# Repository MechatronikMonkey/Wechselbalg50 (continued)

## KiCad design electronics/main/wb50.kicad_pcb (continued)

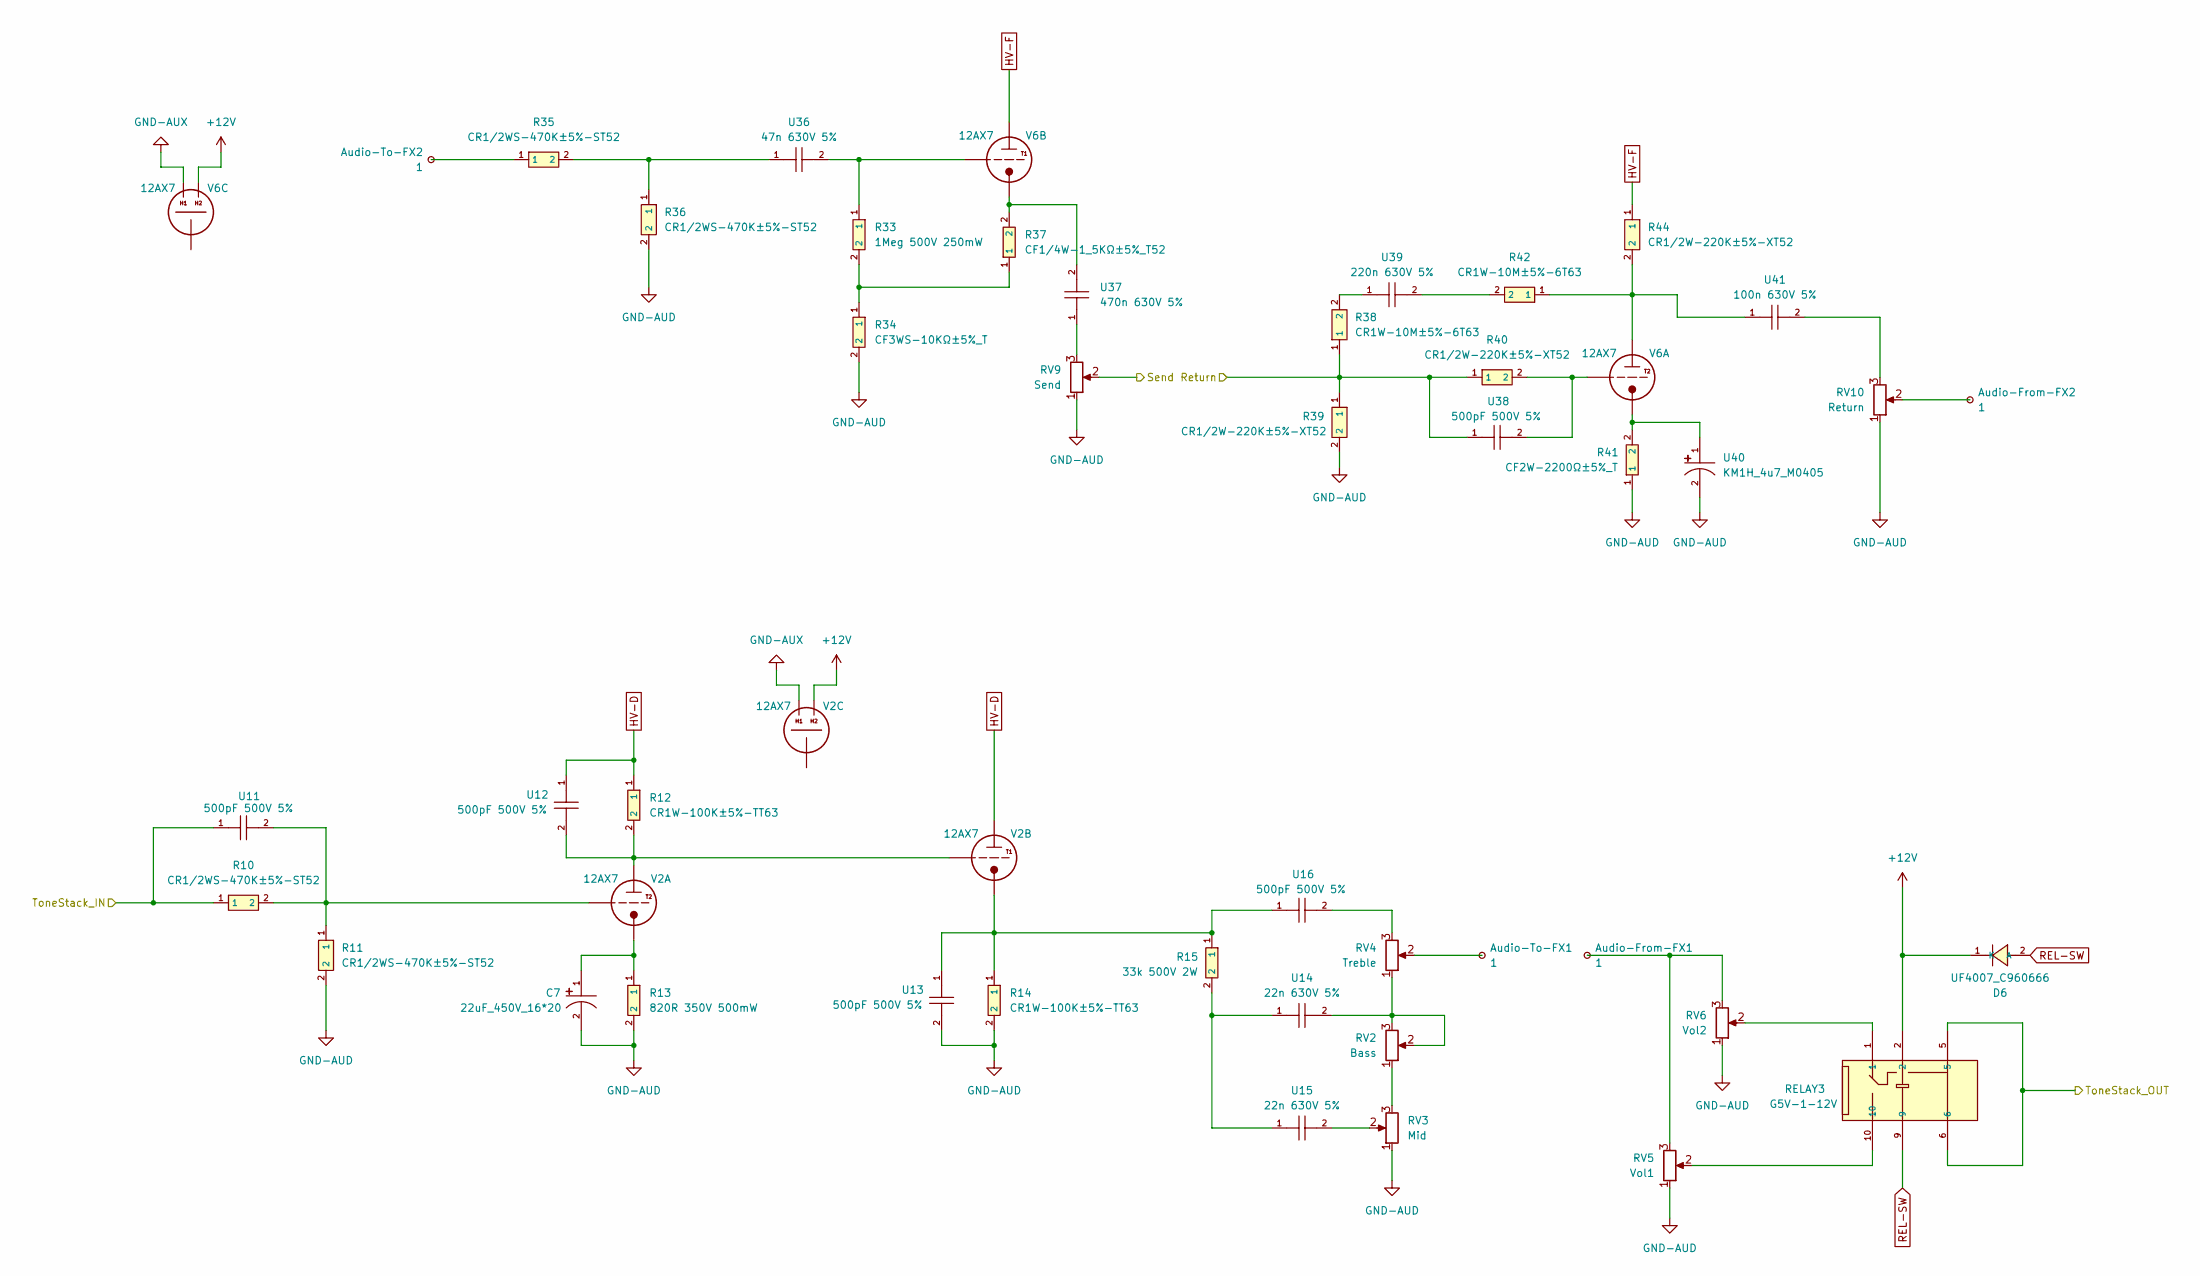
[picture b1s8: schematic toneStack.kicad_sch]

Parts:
Audio-From-FX1, Audio-From-FX2: 1; TestPoint_THTPad_D3.0mm_Drill1.5mm
Audio-To-FX1, Audio-To-FX2: 1; TestPoint_THTPad_D3.0mm_Drill1.5mm
C7: 22uF_450V_16*20; CAP-TH_BD16.0-P7.50-D1.2-FD; LCSC C10737
D6: UF4007_C960666; DO-41_BD2.4-L4.7-P8.70-D0.9-RD; LCSC C960666
R10, R11, R35, R36: CR1/2WS-470K±5%-ST52; RES-TH_BD2.7-L6.2-P10.20-D0.4; LCSC C2857409
R12, R14: CR1W-100K±5%-TT63; RES-TH_BD4.5-L11.0-P15.00-D0.7; LCSC C601829
R13: 820R 350V 500mW; RES-TH_BD4.0-L10.5-P14.50-D0.6; LCSC C167619
R15: 33k 500V 2W; RES-TH_BD3.0-L9.5-P13.50-D0.6; LCSC C70845
R33: 1Meg 500V 250mW; RES-TH_BD2.4-L6.3-P10.30-D0.6; LCSC C1370556
R34: CF3WS-10KΩ±5%_T; RES-TH_BD5.5-L15.0-P19.00-D0.8; LCSC C120810
R37: CF1/4W-1_5KΩ±5%_T52; RES-TH_BD2.3-L6.5-P10.50-D0.5; LCSC C120059
R38, R42: CR1W-10M±5%-6T63; RES-TH_BD4.5-L11.0-P15.00-D0.7; LCSC C2897121
R39, R40, R44: CR1/2W-220K±5%-XT52; RES-TH_BD3.5-L9.0-P13.00-D0.5; LCSC C2894491
R41: CF2W-2200Ω±5%_T; RES-TH_BD5.5-L15.0-P19.00-D0.8; LCSC C187501
RELAY3: G5V-1-12V; RELAY-TH_G5V-1; LCSC C31113
RV2: Bass; WB50_Pot_Omeg_PC20BU_P5.00mm
RV3: Mid; WB50_Pot_Omeg_PC20BU_P5.00mm
RV4: Treble; WB50_Pot_Omeg_PC20BU_P5.00mm
RV5: Vol1; WB50_Pot_Omeg_PC20BU_P5.00mm
RV6: Vol2; WB50_Pot_Omeg_PC20BU_P5.00mm
RV9: Send; WB50_Pot_Omeg_PC20BU_P5.00mm
RV10: Return; WB50_Pot_Omeg_PC20BU_P5.00mm
U11, U12, U13, U16, U38: 500pF 500V 5%; MICA_CAP_L15.5_W3.6_P8.7
U14, U15: 22n 630V 5%; MUSTARD_CAP_D8.5_L20.5_P25.5
U36: 47n 630V 5%; MUSTARD_CAP_D8.5_L20.5_P25.5
U37: 470n 630V 5%; MUSTARD_CAP_D10_L32_P40.4
U39: 220n 630V 5%; MUSTARD_CAP_D10_L32_P40.4
U40: KM1H_4u7_M0405; CAP-TH_BD4.0-P1.50-D0.5-FD; LCSC C2873979
U41: 100n 630V 5%; MUSTARD_CAP_D10_L32_P40.4
V2, V6: 12AX7; WB50_Socket_Noval_9Pin_D21.0mm_Hole1.8mm

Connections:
+12V: D6.1 (K), RELAY3.2, V2.4 (H1), V6.4 (H1); also elsewhere on the board
/Connectors/Return: R38.1, R39.1, R40.1, U38.1; also elsewhere on the board
/Connectors/Send: RV9.2; also elsewhere on the board
/Phase Inverter/PI_IN: RELAY3.5, RELAY3.6; also elsewhere on the board
/Pre Amp/PreAmp_OUT: R10.1, U11.1; also elsewhere on the board
GND-AUD: C7.2, R11.2, R13.2, R14.2, R34.2, R36.2, R39.2, R41.1, RV3.1, RV5.1, RV6.1, RV9.1, RV10.1, U13.2, U40.2; also elsewhere on the board
GND-AUX: V2.5 (H2), V6.5 (H2); also elsewhere on the board
HV-D: R12.1, U12.1, V2.6 (A/P); also elsewhere on the board
HV-F: R44.1, V6.6 (A/P); also elsewhere on the board
unnamed: Audio-From-FX1.1, RV5.3, RV6.3
unnamed: Audio-From-FX2.1, RV10.2
unnamed: Audio-To-FX1.1, RV4.2
unnamed: Audio-To-FX2.1, R35.1
unnamed: R15.2, U14.1, U15.1
unnamed: R33.2, R34.1, R37.1
unnamed: R35.2, R36.1, U36.1
unnamed: R38.2, U39.1
unnamed: R42.2, U39.2
unnamed: RELAY3.1, RV6.2
unnamed: RELAY3.10, RV5.2
unnamed: RV2.1, RV3.3
unnamed: RV2.2, RV2.3, RV4.1, U14.2
unnamed: RV3.2, U15.2
unnamed: RV4.3, U16.2
unnamed: RV9.3, U37.1
unnamed: RV10.3, U41.2
unnamed: R12.2, U12.2, V2.1 (A/P), V2.7 (G)
unnamed: C7.1, R13.1, V2.3 (C/K)
unnamed: R10.2, R11.1, U11.2, V2.2 (G)
unnamed: R14.1, R15.1, U13.1, U16.1, V2.8 (C/K)
unnamed: R42.1, R44.2, U41.1, V6.1 (A/P)
unnamed: R41.2, U40.1, V6.3 (C/K)
unnamed: R40.2, U38.2, V6.2 (G)
unnamed: R37.2, U37.2, V6.8 (C/K)
unnamed: R33.1, U36.2, V6.7 (G)
REL-SW: D6.2 (A), RELAY3.9; also elsewhere on the board

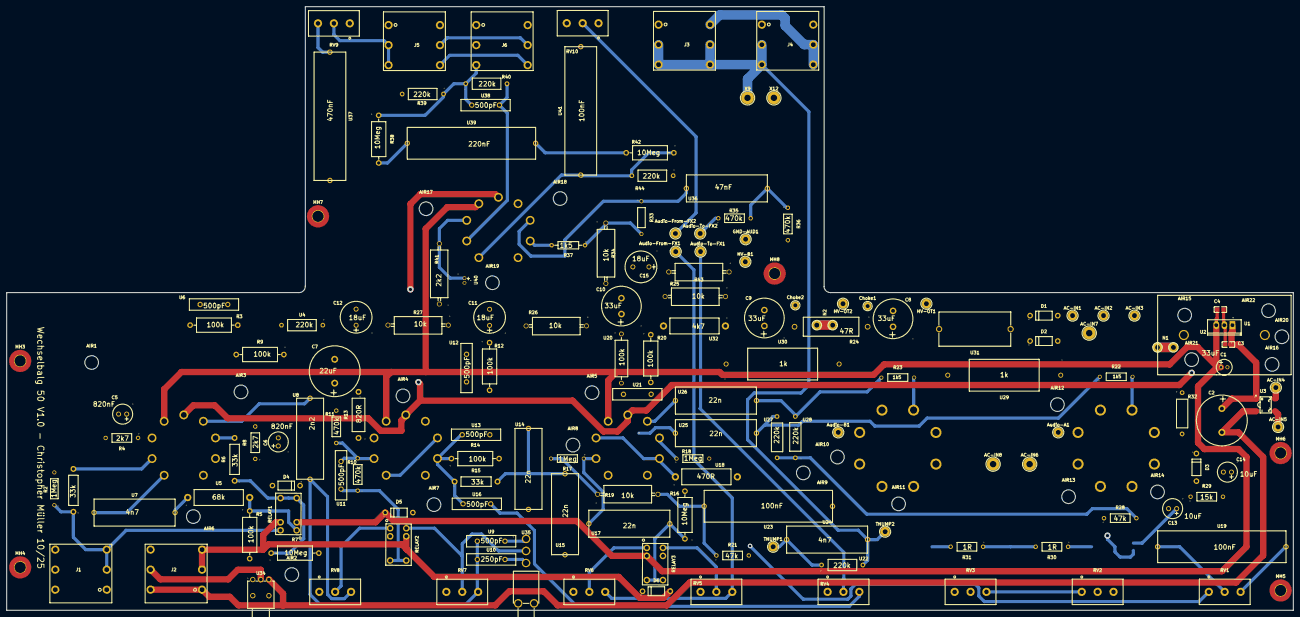
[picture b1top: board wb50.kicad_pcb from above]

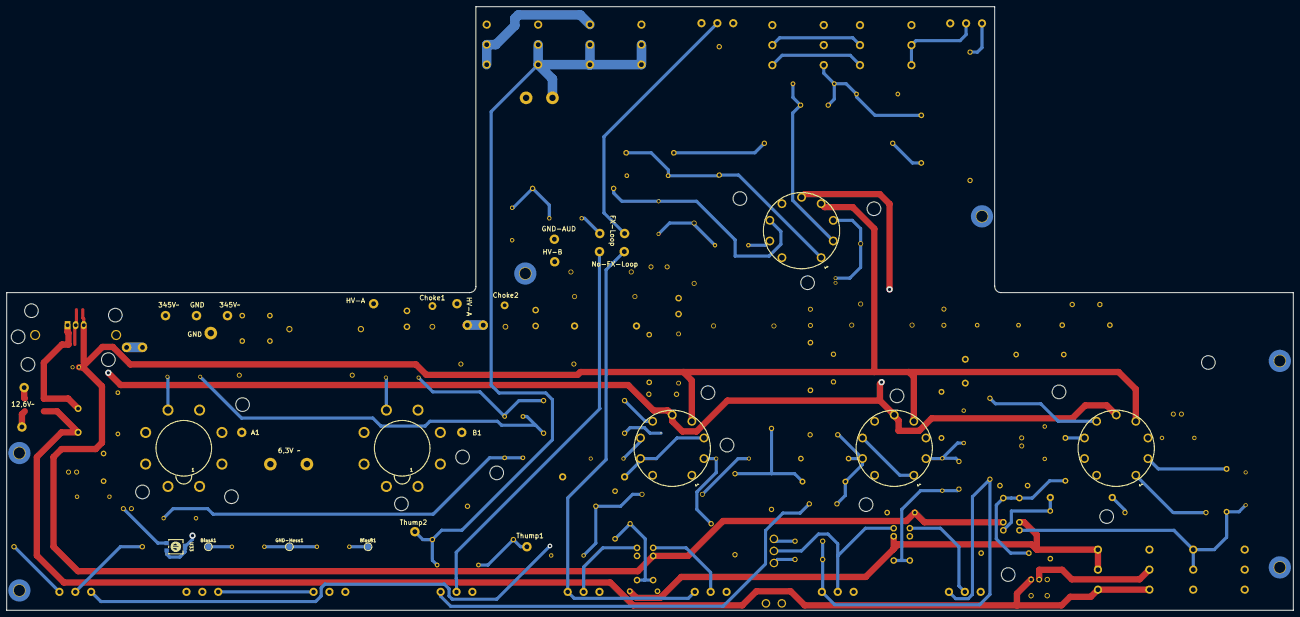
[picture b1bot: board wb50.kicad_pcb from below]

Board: 4 copper layers, 405.0 x 190.0 mm, 188 parts (10 on the bottom side), 94 nets.

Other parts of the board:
Audio-A1: 1; TestPoint_THTPad_D3.0mm_Drill1.5mm
Audio-B1: 1; TestPoint_THTPad_D3.0mm_Drill1.5mm
BiasA1: 1; TestPoint_Pad_D2.0mm
BiasB1: 1; TestPoint_Pad_D2.0mm
GND-Mess1: 1; TestPoint_Pad_D2.0mm
HV-OT1, HV-OT2: 1; TestPoint_THTPad_D3.0mm_Drill1.5mm
U35: MT-0-103-C004-N004-RS; SW-TH_MT-0-102-C004-N004-RS

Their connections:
GND-AUD: GND-Mess1.1; also elsewhere on the board
HV-A: HV-OT1.1, HV-OT2.1; also elsewhere on the board
unnamed 52: U35.2; also elsewhere on the board
unnamed 65: U35.3; also elsewhere on the board
unnamed 66: U35.1; also elsewhere on the board
unnamed 82: Audio-A1.1; also elsewhere on the board
unnamed 85: BiasA1.1; also elsewhere on the board
unnamed 86: Audio-B1.1; also elsewhere on the board
unnamed 89: BiasB1.1; also elsewhere on the board

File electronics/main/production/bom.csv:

Designator,Footprint,Quantity,Value,LCSC Part #
"AC-IN1, AC-IN2, AC-IN3, AC-IN4, AC-IN5, AUDIO-A1, AUDIO-B1, AUDIO-FROM-FX1, AUDIO-FROM-FX2, AUDIO-TO-FX1, AUDIO-TO-FX2, GND-AUD1, HV-B1, HV-OT1, HV-OT2, THUMP1, THUMP2",TestPoint_THTPad_D3.0mm_Drill1.5mm,17,1,
"AC-IN6, AC-IN7, AC-IN8",TestPoint_THTPad_D4.0mm_Drill2.0mm,3,1,
"AIR1, AIR10, AIR11, AIR12, AIR13, AIR14, AIR15, AIR16, AIR17, AIR18, AIR19, AIR2, AIR20, AIR21, AIR22, AIR3, AIR4, AIR5, AIR6, AIR7, AIR8, AIR9",MountingHole_4.3mm_M4,22,VentingHole,
"BIASA1, BIASB1, GND-MESS1",TestPoint_Pad_D2.0mm,3,1,
C1,CAP-TH_BD5.0-P2.00-D0.8-FD,1,33uF 50V,C89792
"C10, C8, C9",CAP-TH_BD12.5-P5.00-D0.6-FD,3,33uF 500V 5R5-ESR,C443401
"C11, C12, C15",CAP-TH_BD10.0-P5.00-D1.0-FD,3,18uF 450V ±20%,C781269
"C13, C14",CAP-TH_BD6.3-P2.50-D1.0-FD,2,10uf/100V,C2029
C2,CAP-TH_BD16.0-P7.50-D1.2-FD,1,LKMI2501C682MF,C442803
"C3, C4",C0805,2,CC0805KRX7R9BB104,C49678
"C5, C6",CAP-TH_BD6.3-P2.50-D1.0-FD,2,"0,82uF 400V 20 %",C2029
C7,CAP-TH_BD16.0-P7.50-D1.2-FD,1,22uF_450V_16*20,C10737
"CHOKE1, CHOKE2",TestPoint_THTPad_D2.5mm_Drill1.2mm,2,1,
"D1, D2, D3, D4, D5, D6",DO-41_BD2.4-L4.7-P8.70-D0.9-RD,6,UF4007_C960666,C960666
J1,WB50_Jack_TRS_6pin_16.2mm,1,IN,
J2,WB50_Jack_TRS_6pin_16.2mm,1,SW,
J3,WB50_Jack_TRS_6pin_16.2mm,1,OUT1,
J4,WB50_Jack_TRS_6pin_16.2mm,1,OUT2,
J5,WB50_Jack_TRS_6pin_16.2mm,1,Send,
J6,WB50_Jack_TRS_6pin_16.2mm,1,Return,
"MH3, MH4, MH5, MH6, MH7, MH8",MountingHole_3.5mm_Pad_TopBottom,6,MountHole,
"N1, N2",NetTie_0.5mm_2Pad,2,~,
"R1, R15, R6",RES-TH_BD3.0-L9.5-P13.50-D0.6,3,33k 500V 2W,C70845
"R10, R11, R35, R36",RES-TH_BD2.7-L6.2-P10.20-D0.4,4,CR1/2WS-470K±5%-ST52,C2857409
"R12, R14, R20, R3, R5, R9",RES-TH_BD4.5-L11.0-P15.00-D0.7,6,CR1W-100K±5%-TT63,C601829
R13,RES-TH_BD4.0-L10.5-P14.50-D0.6,1,820R 350V 500mW,C167619
"R16, R38, R42, R7",RES-TH_BD4.5-L11.0-P15.00-D0.7,4,CR1W-10M±5%-6T63,C2897121
"R17, R18, R2, R33",RES-TH_BD2.4-L6.3-P10.30-D0.6,4,1Meg 500V 250mW,C1370556
"R19, R25, R26, R27, R34",RES-TH_BD5.5-L15.0-P19.00-D0.8,5,CF3WS-10KΩ±5%_T,C120810
"R21, R28",RES-TH_BD2.7-L6.2-P10.20-D0.4,2,CR1/4W-47K±5%-ST52,C2896823
"R22, R23",RES-TH_BD2.4-L6.3-P10.30-D0.6,2,CFR-25JT-52-1K5,C1370569
R24,RES-TH_BD6.0-L17.5-P21.50-D0.8,1,MOF5WS-47Ω±5%,C121969
R29,RES-TH_BD2.7-L6.2-P10.20-D0.4,1,CR1/4W-15K±5%-OT52,C2894565
"R30, R31",RES-TH_BD2.7-L6.2-P10.20-D0.4,2,MF1/4W-1Ω±1%-ST26,C2903254
"R32, R39, R40, R44, U22, U27, U28, U4",RES-TH_BD3.5-L9.0-P13.00-D0.5,8,CR1/2W-220K±5%-XT52,C2894491
R37,RES-TH_BD2.3-L6.5-P10.50-D0.5,1,CF1/4W-1_5KΩ±5%_T52,C120059
"R4, R8",RES-TH_BD2.7-L6.2-P10.20-D0.4,2,CR1/4W-2K7±5%-ST26,C2894624
"R41, R43",RES-TH_BD5.5-L15.0-P19.00-D0.8,2,CF2W-2200Ω±5%_T,C187501
"RELAY1, RELAY2, RELAY3",RELAY-TH_G5V-1,3,G5V-1-12V,C31113
RV1,WB50_Pot_Omeg_PC20BU_P5.00mm,1,Presence,
RV10,WB50_Pot_Omeg_PC20BU_P5.00mm,1,Return,
RV2,WB50_Pot_Omeg_PC20BU_P5.00mm,1,Bass,
RV3,WB50_Pot_Omeg_PC20BU_P5.00mm,1,Mid,
RV4,WB50_Pot_Omeg_PC20BU_P5.00mm,1,Treble,
RV5,WB50_Pot_Omeg_PC20BU_P5.00mm,1,Vol1,
RV6,WB50_Pot_Omeg_PC20BU_P5.00mm,1,Vol2,
RV7,WB50_Pot_Omeg_PC20BU_P5.00mm,1,Gain1,
RV8,WB50_Pot_Omeg_PC20BU_P5.00mm,1,Gain2,
RV9,WB50_Pot_Omeg_PC20BU_P5.00mm,1,Send,
U1,HEATSINK-TH_XSD366-094,1,XSD366-094,C286227
U10,MICA_CAP_L15.5_W3.6_P8.7,1,250pF 500V 5%,
"U11, U12, U13, U16, U38, U6, U9",MICA_CAP_L15.5_W3.6_P8.7,7,500pF 500V 5%,
"U14, U15, U17, U25, U26",MUSTARD_CAP_D8.5_L20.5_P25.5,5,22n 630V 5%,
U18,RES-TH_BD5.0-L15.5-P19.50-D0.7,1,470R 500V 2W,C2905226
"U19, U23, U41",MUSTARD_CAP_D10_L32_P40.4,3,100n 630V 5%,
U2,TO-220-3_L10.0-W4.5-P2.54-L,1,L7812CV-DG,C2914
U20,RES-TH_BD4.0-L11.5-P15.50-D0.7,1,CF2WS-82KΩ±5%_T,C120647
U21,MICA_CAP_L15.5_W3.6_P8.7,1,100pF 500V 5%,
"U24, U7",MUSTARD_CAP_D8.5_L20.5_P25.5,2,4n7 630V 5%,
"U29, U30",RES-TH_BD9.5-L22.0-P26.00-D0.7,2,CR-L5W-1KΩJ,C334294
U3,ABS-SMD_L5.0-W4.4-P4.00-LS7.0-BL,1,AB24S,C882375
U31,FUSE-TH_L22.5-W10.8-P22.50_0031.8201.G,1,16A 20mm 500V 5mm Plugin Fuse,C3204125
U32,RES-TH_BD5.0-L15.5-P19.50-D0.7,1,CR2W-4K7±5%-9T73,C2903451
U33,RES-ADJ-SMD_3314G-1-103E,1,3314G-1-503E,C719184
U34,SW-TH_ST-0-102-C03-N003-RS,1,ST-0-102-C03-N003-RS,C1788489
U35,SW-TH_MT-0-102-C004-N004-RS,1,MT-0-103-C004-N004-RS,C22448931
U36,MUSTARD_CAP_D8.5_L20.5_P25.5,1,47n 630V 5%,
U37,MUSTARD_CAP_D10_L32_P40.4,1,470n 630V 5%,
U39,MUSTARD_CAP_D10_L32_P40.4,1,220n 630V 5%,
U40,CAP-TH_BD4.0-P1.50-D0.5-FD,1,KM1H_4u7_M0405,C2873979
U5,RES-TH_BD5.0-L15.5-P19.50-D0.7,1,CR2W-68K±5%-9T73,C2903458
U8,MUSTARD_CAP_D8.5_L20.5_P25.5,1,2n2 630V 5%,
"V1, V2, V3, V6",WB50_Socket_Noval_9Pin_D21.0mm_Hole1.8mm,4,12AX7,
"V4, V5",WB50_Socket_Octal_8Pin_D26.0mm_Hole2.0mm,2,EL34,
X12,TestPoint_THTPad_D4.0mm_Drill2.0mm,1,GND_OT,
X9,TestPoint_THTPad_D4.0mm_Drill2.0mm,1,Audio IN,

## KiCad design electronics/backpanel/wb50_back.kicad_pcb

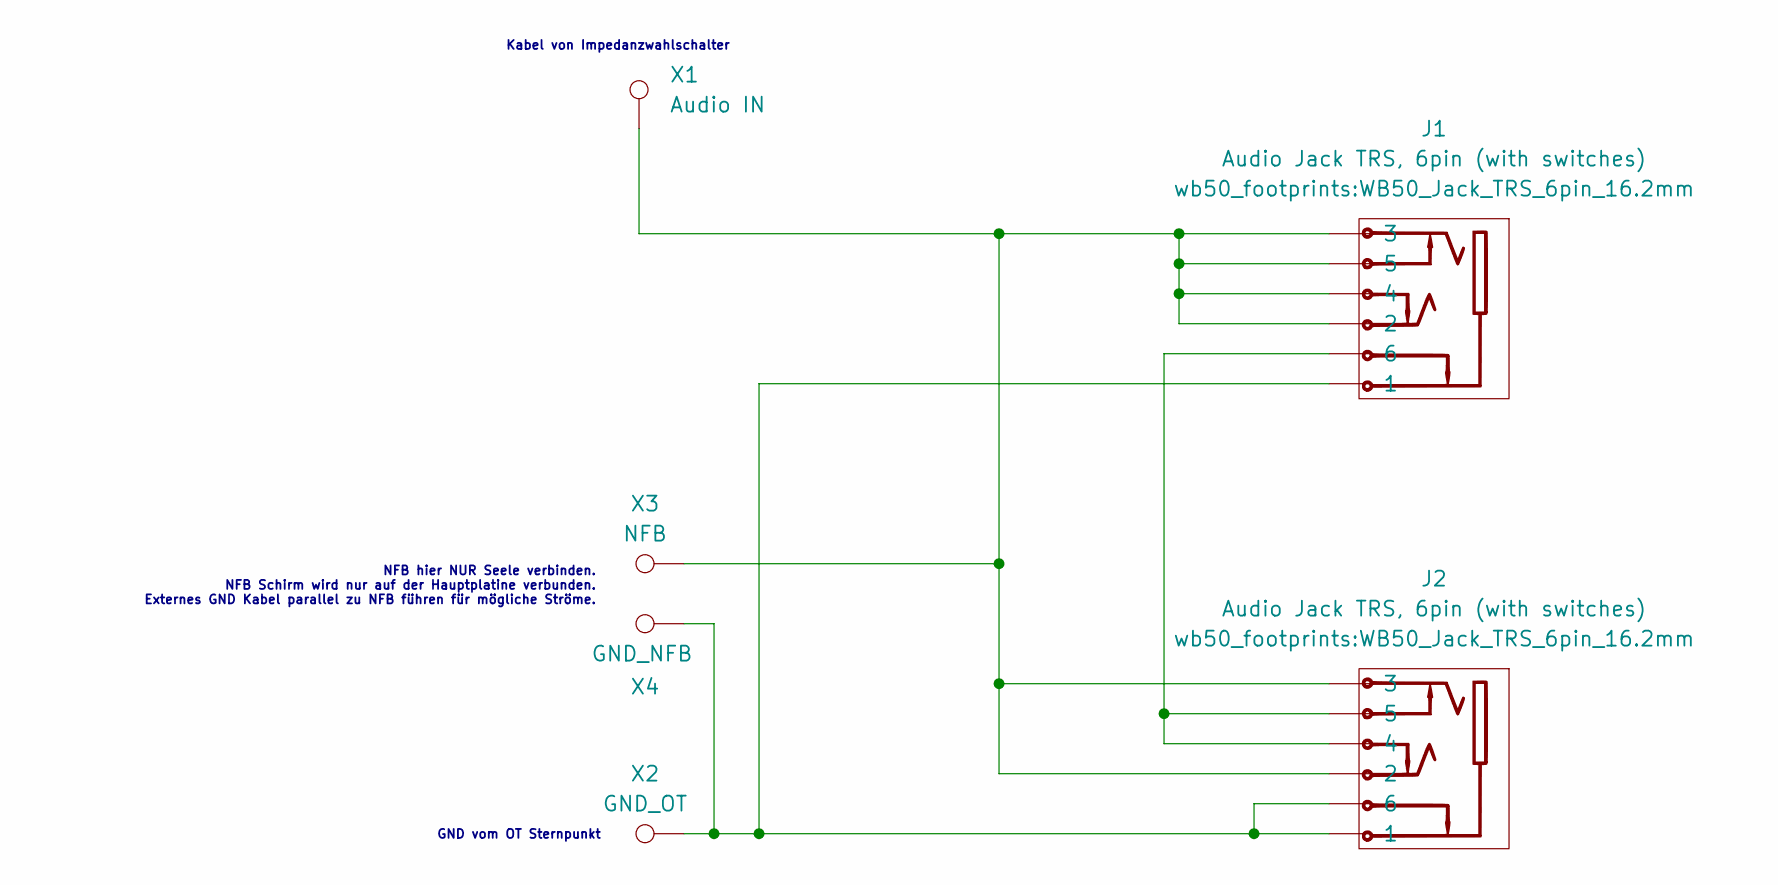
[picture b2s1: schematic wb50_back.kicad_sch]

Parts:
J1, J2: Audio Jack TRS, 6pin (with switches); WB50_Jack_TRS_6pin_16.2mm
X1: Audio IN; TestPoint_THTPad_D4.0mm_Drill2.0mm
X2: GND_OT; TestPoint_THTPad_D4.0mm_Drill2.0mm
X3: NFB; TestPoint_THTPad_D1.5mm_Drill0.7mm
X4: GND_NFB; TestPoint_THTPad_D4.0mm_Drill2.0mm

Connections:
unnamed: J1.1, J2.1, J2.6, X2.1, X4.1
unnamed: J1.2, J1.3, J1.4, J1.5, J2.2, J2.3, X1.1, X3.1
unnamed: J1.6, J2.4, J2.5

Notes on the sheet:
Kabel von Impedanzwahlschalter
NFB hier NUR Seele verbinden. NFB Schirm wird nur auf der Hauptplatine verbunden. Externes GND Kabel parallel zu NFB führen für mögliche Ströme.
GND vom OT Sternpunkt

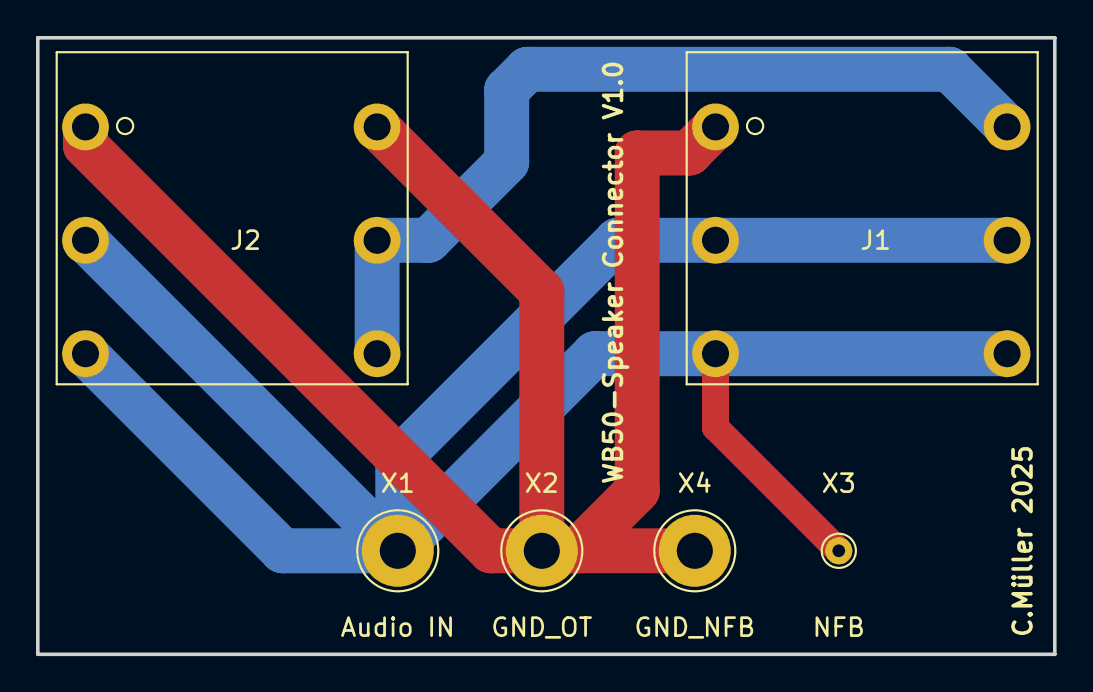
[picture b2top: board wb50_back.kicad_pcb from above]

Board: 2 copper layers, 56.5 x 34.2 mm, 6 parts (0 on the bottom side), 3 nets.

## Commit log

2025-09-26 Revise README for Wechselbalg 50 amplifier
    Expanded the README to provide detailed information about the Wechselbalg 50 amplifier, including highlights, circuit overview, safety precautions, and project scope.
2025-09-27 KiCad project created and basic setup with basic parts
2025-09-27 kosten update
2025-09-27 fonts for front plate
2025-09-27 front plate design
2025-09-28 frontpanel parts placed and locked
2025-09-28 bring potentiometers more to front and lock again
2025-09-28 adjust pcb size
2025-09-28 exported step for shield platings
2025-09-28 updated pcb size
2025-09-28 update step with new pcb size
2025-09-28 shield plating added
2025-09-29 update cost
2025-09-29 rename drawings (remove)
2025-09-30 restructure
2025-09-30 restructure 2
2025-09-30 restructure finish
2025-09-30 routed
2025-09-30 setup jlcpcb
2025-09-30 aux voltage
2025-09-30 update aux voltage
2025-10-01 widerstände angelegt
2025-10-03 PI stage ready
2025-10-05 schematic ready? - check
2025-10-05 schematic checked!
2025-10-08 updated PCB
2025-10-10 update housing, speakers and schematics
2025-10-10 update design
2025-10-12 add fx loop, add new shield
2025-10-17 update kosten und letzte bestellungen für Teile
